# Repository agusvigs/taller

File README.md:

# MonitorFrigorifico

## Descripción
MonitorFrigorifico es un proyecto electrónico que utiliza un ESP32 para controlar la temperatura y el estado de la puerta de un frigorífico. Su objetivo es detectar temperaturas elevadas y puertas abiertas durante demasiado tiempo, activando una alarma para avisar al usuario.

## Funciones principales
- Medición de temperatura mediante un sensor DS18B20.
- Detección de apertura y cierre de la puerta mediante un Reed Switch.
- Activación de una alarma sonora cuando la temperatura supera el límite establecido.
- Aviso cuando la puerta permanece abierta durante más de un minuto.
- Visualización de información en una pantalla LCD de 16x2.
- Conexión Wi-Fi para consultar los datos desde una aplicación.

## Componentes
- ESP32.
- Sensor de temperatura DS18B20.
- Reed Switch.
- Buzzer.
- Pantalla LCD 16x2 con módulo I2C.
- Placa de circuito impreso (PCB).
- Cables y alimentación eléctrica.

## Archivos del proyecto
- `frigorifico.ino`: código del programa para el ESP32.
- `Vigistain 3D.stl`: modelo tridimensional de la caja para imprimir en 3D.
- `proyecto ref`: carpeta con archivos de referencia del proyecto.

## Funcionamiento
El ESP32 recibe los datos del sensor de temperatura y del Reed Switch. Si detecta una temperatura superior al límite configurado o una puerta abierta durante demasiado tiempo, activa el buzzer. La pantalla LCD muestra información sobre la temperatura y el estado de la puerta. Mediante Wi-Fi, los datos también pueden consultarse desde una aplicación compatible.

## Objetivo
Desarrollar un sistema electrónico que permita supervisar las condiciones de un frigorífico y alertar al usuario ante situaciones que puedan afectar su funcionamiento.

## Instalación y uso
1. Conectar los componentes al ESP32 según el circuito diseñado.
2. Abrir `frigorifico.ino` en el IDE de Arduino.
3. Configurar las credenciales de la red Wi-Fi en el código.
4. Seleccionar la placa ESP32 y el puerto correspondiente.
5. Cargar el programa en el ESP32.
6. Encender el sistema y comprobar el funcionamiento de los sensores, la pantalla y la alarma.

## Modelo 3D
El archivo `Vigistain 3D.stl` contiene el diseño de la caja, preparado para utilizarse en un programa de laminado e impresión 3D. Antes de imprimir, se recomienda verificar las dimensiones y la ubicación de los componentes.

## Autores
Proyecto realizado por Agustin Vigistain y Bautista Fusi, como trabajo final de Taller de 5.º año.

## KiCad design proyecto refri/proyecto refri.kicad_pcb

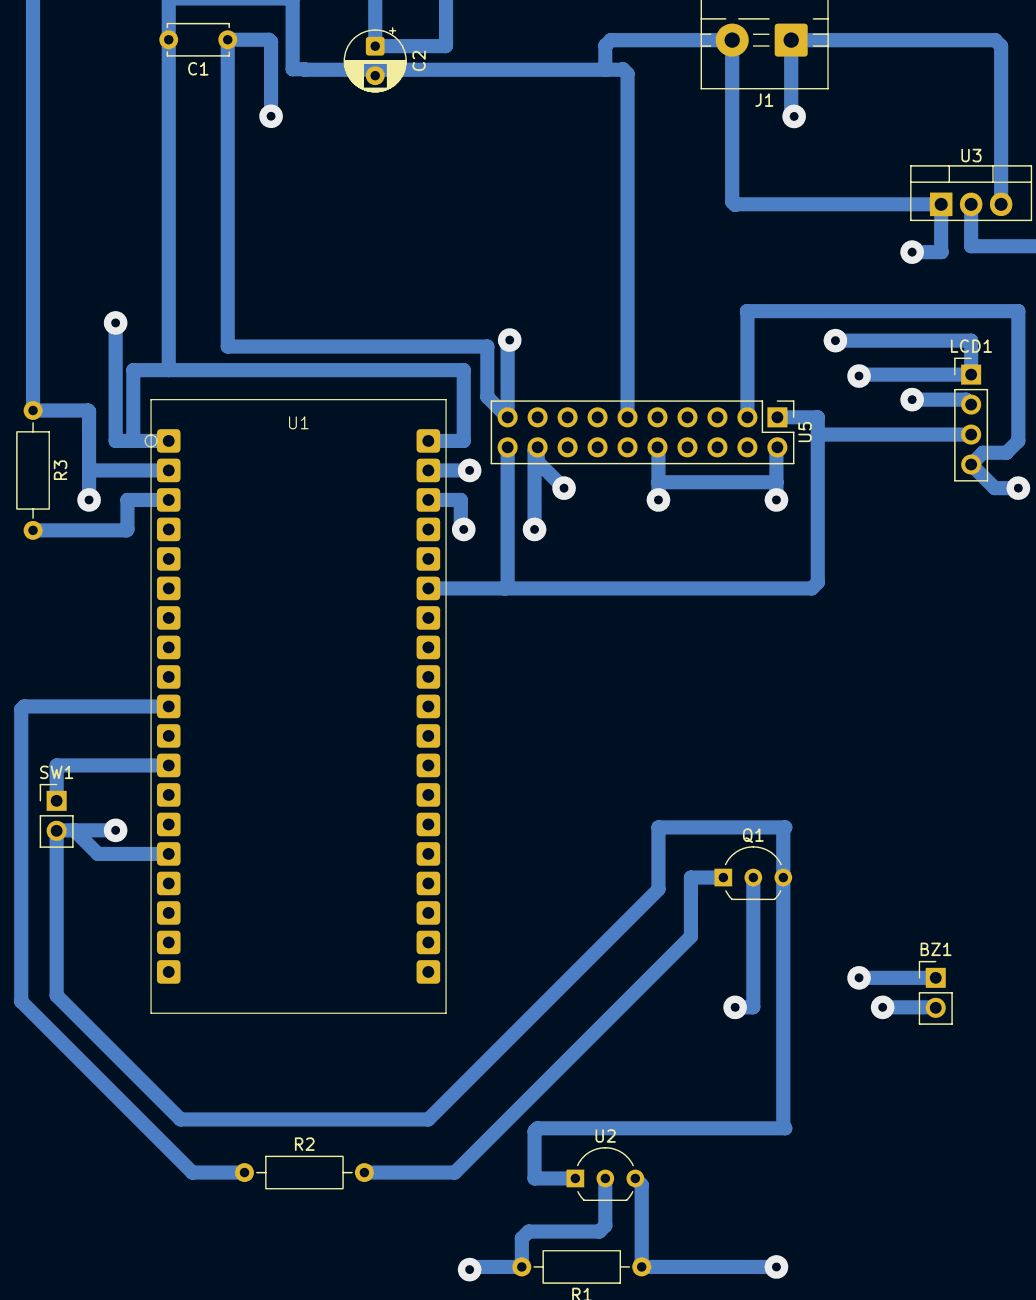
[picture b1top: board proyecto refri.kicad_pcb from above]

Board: 2 copper layers, 14 parts (0 on the bottom side), 11 nets.

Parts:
BZ1: Buzzer; PinHeader_1x02_P2.54mm_Vertical
C1: 100nF; C_Disc_D5.0mm_W2.5mm_P5.00mm
C2: 100uF; CP_Radial_D5.0mm_P2.50mm
J1: ENTRADA 5V; TerminalBlock_MaiXu_MX126-5.0-02P_1x02_P5.00mm
LCD1: LCD_I2C; PinHeader_1x04_P2.54mm_Vertical
Q1: Q_NPN_BCE; TO-92_Inline_Wide
R1: 4.7K; R_Axial_DIN0207_L6.3mm_D2.5mm_P10.16mm_Horizontal
R2: 1K; R_Axial_DIN0207_L6.3mm_D2.5mm_P10.16mm_Horizontal
R3: 10K; R_Axial_DIN0207_L6.3mm_D2.5mm_P10.16mm_Horizontal
SW1: SW_Reed; PinHeader_1x02_P2.54mm_Vertical
U1: ESP32-WROOM-32; ESP32_38Pin
U2: DS18B20; TO-92_Inline_Wide
U3: AMS1117-3.3; TO-220-3_Vertical
U5: TXS0108EPW; PinHeader_2x10_P2.54mm_Vertical

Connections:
+3V3: C2.1, R1.1, R3.1, U1.2 (VDD), U2.3 (V_{DD}), U3.2 (VO), U5.2 (VCCA), U5.10 (OE)
+5V: BZ1.1 (+), C1.1, J1.1, LCD1.1, U3.3 (VI), U5.19 (VCCB)
/SCL: LCD1.4, U1.36 (IO22), U5.3 (A2), U5.18 (B2)
/SDA: LCD1.3, U1.33 (IO21), U5.1 (A1), U5.20 (B1)
GND: C1.2, C2.2, J1.2, LCD1.2, Q1.3 (E), SW1.2, U1.1 (GND), U1.15 (GND), U1.38 (GND), U2.1 (GND), U3.1 (GND), U5.11 (GND)
unnamed: BZ1.2 (-), Q1.2 (C)
unnamed: Q1.1 (B), R2.2
unnamed: R3.2, U1.3 (EN)
unnamed: R1.2, U1.37 (IO23), U2.2 (DQ)
unnamed: R2.1, U1.10 (IO25)
unnamed: SW1.1, U1.12 (IO27)
